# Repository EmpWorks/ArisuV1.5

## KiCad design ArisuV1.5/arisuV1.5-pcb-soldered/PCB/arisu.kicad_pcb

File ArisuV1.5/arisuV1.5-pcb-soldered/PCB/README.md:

# ArisuV1.5 Keyboard PCB
アリス PCB designed using KiCad. The layout is inspired by Lyn's EM7 and TGR Alice with some modification of my own.
Originally created by FateNozomi
### Disclaimer 
This board is a heavily-modified FateNozomi arisu-pcb While the schematic, basic layout etc is essentially the same, it supports additional features like Hot-swap,USB-C etc.

Key differences:
- supports hotswap PCB sockets
- added WS2812B Smd Led footprint for backlit 
- encoder support
- supports atmega32u4 MU/AU
- USB-C compatibility

Disclaimer: Use these files at your own risk.

## Assembly
For the components required, you may refer to the bill of materials here [BOM](https://github.com/donttellmywife1510/ArisuV1.5/blob/main/ArisuV1.5/arisuV1.5-pcb-soldered/PCB/arisu_BOM.xlsx).

All the components can be soldered using a regular soldering iron, lcsc parts list is for reference only.

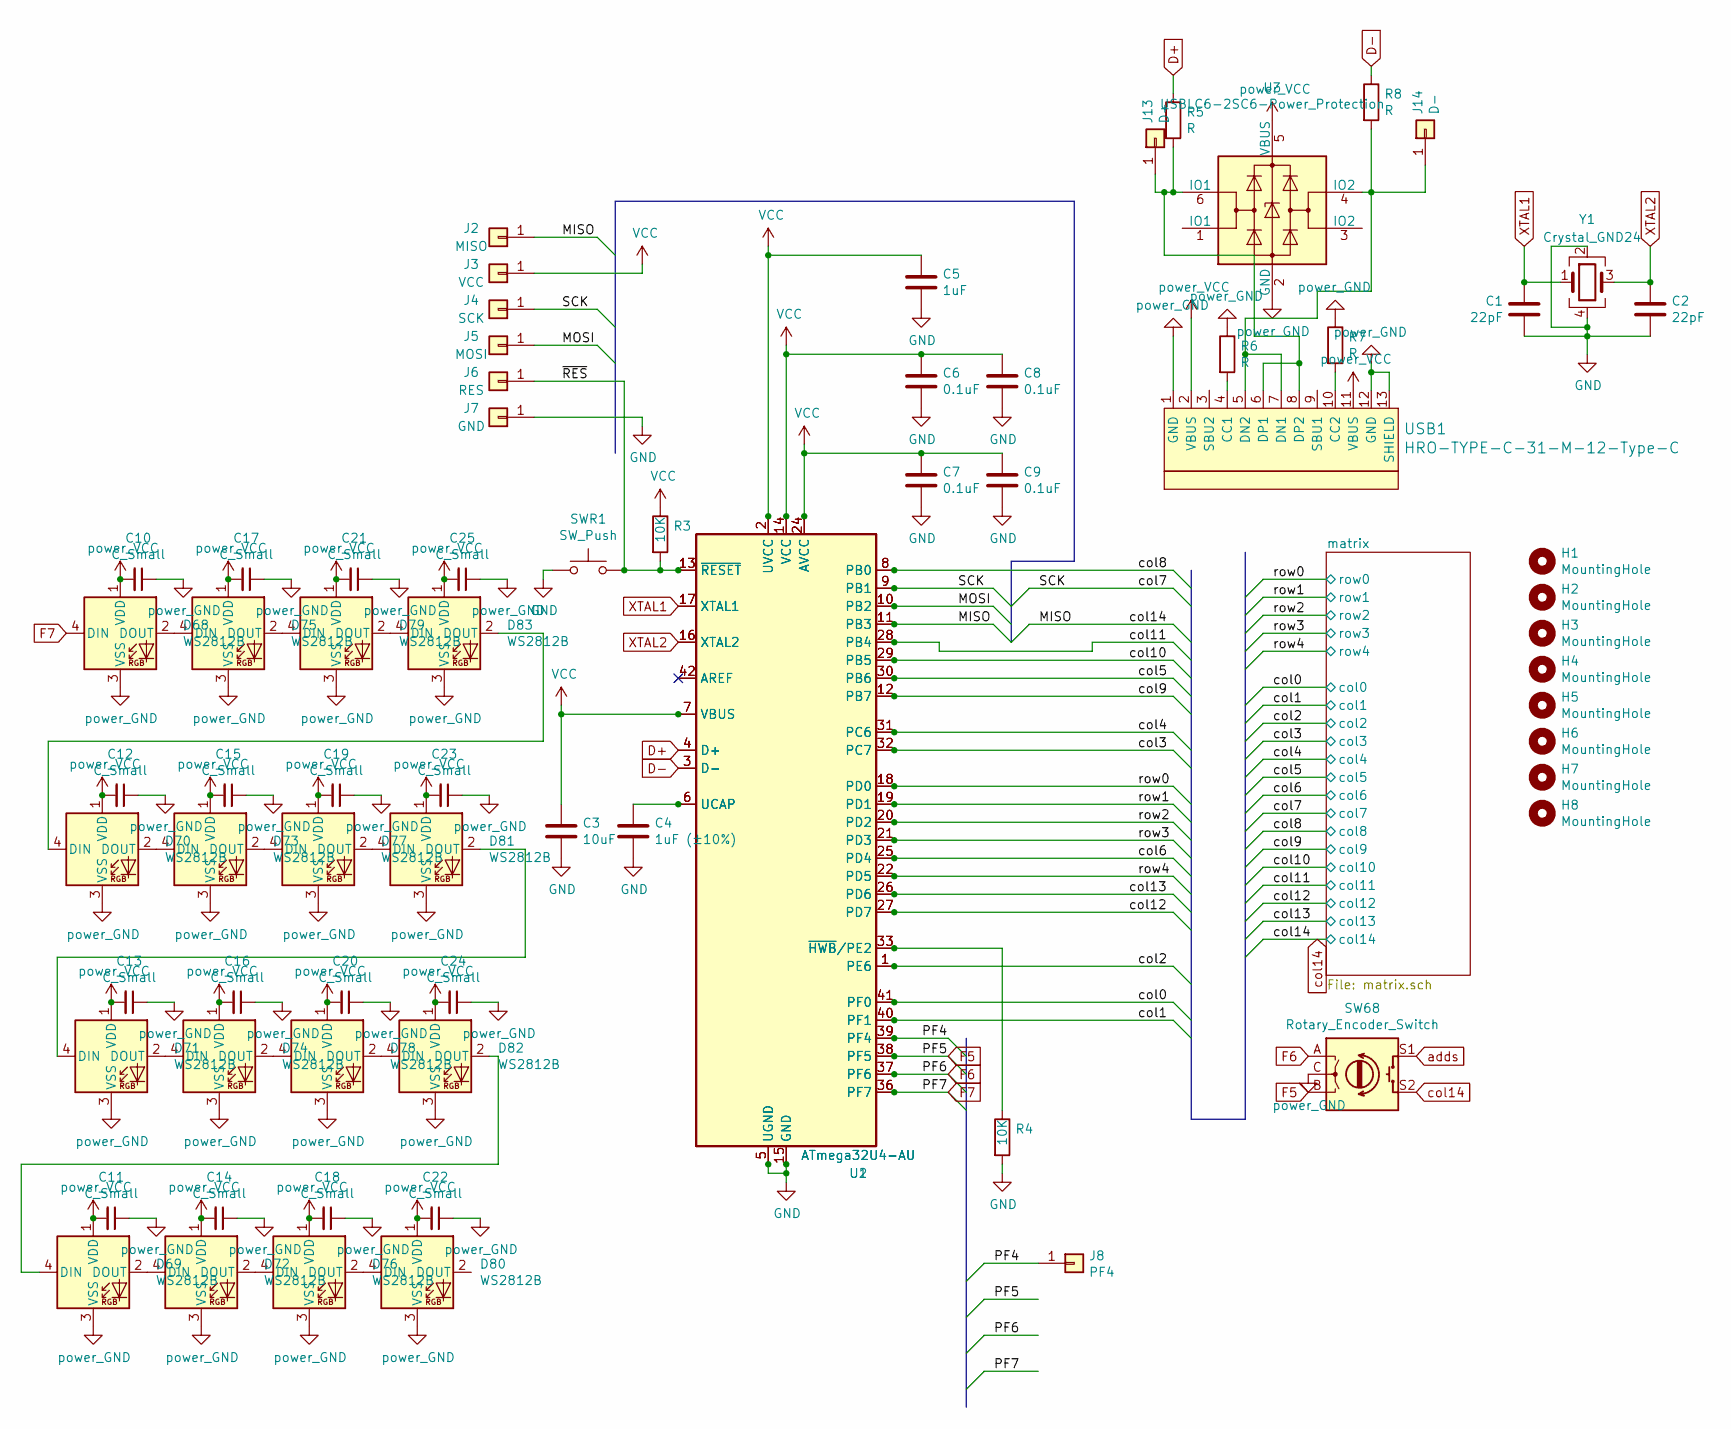
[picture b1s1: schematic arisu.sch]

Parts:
C1, C2: 22pF; C_0805_HandSoldering
C3: 10uF; C_0805_HandSoldering
C4: 1uF (±10%); C_0805_HandSoldering
C5: 1uF; C_0805_HandSoldering
C6, C7, C8, C9: 0.1uF; C_0805_HandSoldering
C10, C11, C12, C13, C14, C15, C16, C17, C18, C19, C20, C21, C22, C23, C24, C25: C_Small; C_0805_2012Metric_Pad1.18x1.45mm_HandSolder
D68, D69, D70, D71, D72, D73, D74, D75, D76, D77, D78, D79, D80, D81, D82, D83: WS2812B; LED_WS2812B_PLCC4_5.0x5.0mm_P3.2mm
H1, H2, H3, H4, H5, H6, H7, H8: MountingHole; MountingHole_2.2mm_M2_Pad
J2: MISO; Pin_Header_Straight_1x01_Pitch2.54mm
J3: VCC; Pin_Header_Straight_1x01_Pitch2.54mm
J4: SCK; Pin_Header_Straight_1x01_Pitch2.54mm
J5: MOSI; Pin_Header_Straight_1x01_Pitch2.54mm
J6: RES; Pin_Header_Straight_1x01_Pitch2.54mm
J7: GND; Pin_Header_Straight_1x01_Pitch2.54mm
J8: PF4; Pin_Header_Straight_1x01_Pitch2.54mm
J13: D+; Pin_Header_Straight_1x01_Pitch2.54mm
J14: D-; Pin_Header_Straight_1x01_Pitch2.54mm
R3, R4: 10K; R_0805_HandSoldering
R5, R6, R7, R8: R; R_0805_2012Metric_Pad1.20x1.40mm_HandSolder
SW68: Rotary_Encoder_Switch; RotaryEncoder_Alps_EC12E-Switch_Vertical_H20mm
SWR1: SW_Push; SW_SPST_TL3342
U1: ATmega32U4-AU; QFN-44-1EP_7x7mm_P0.5mm_EP5.2x5.2mm
U2: ATmega32U4-AU; LQFP-44_10x10mm_P0.8mm
U3: USBLC6-2SC6-Power_Protection; SOT-23-6
USB1: HRO-TYPE-C-31-M-12-Type-C; USB_C_Receptacle_HRO_TYPE-C-31-M-12-HandSoldering
Y1: Crystal_GND24; Crystal_SMD_SeikoEpson_FA238-4pin_3.2x2.5mm_HandSoldering

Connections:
/MOSI: J5.1, U1.10 (PB2), U2.10 (PB2)
/PF4: J8.1, U1.39 (PF4), U2.39 (PF4)
/SCK: J4.1, U1.9 (PB1), U2.9 (PB1); also elsewhere on the board
/col0: U1.41 (PF0), U2.41 (PF0); also elsewhere on the board
/col1: U1.40 (PF1), U2.40 (PF1); also elsewhere on the board
/col2: U1.1 (PE6), U2.1 (PE6); also elsewhere on the board
/col3: U1.32 (PC7), U2.32 (PC7); also elsewhere on the board
/col4: U1.31 (PC6), U2.31 (PC6); also elsewhere on the board
/col5: U1.30 (PB6), U2.30 (PB6); also elsewhere on the board
/col6: U1.25 (PD4), U2.25 (PD4); also elsewhere on the board
/col8: U1.8 (PB0), U2.8 (PB0); also elsewhere on the board
/col9: U1.12 (PB7), U2.12 (PB7); also elsewhere on the board
/col10: U1.29 (PB5), U2.29 (PB5); also elsewhere on the board
/col11: U1.28 (PB4), U2.28 (PB4); also elsewhere on the board
/col12: U1.27 (PD7), U2.27 (PD7); also elsewhere on the board
/col13: U1.26 (PD6), U2.26 (PD6); also elsewhere on the board
/row0: U1.18 (PD0), U2.18 (PD0); also elsewhere on the board
/row1: U1.19 (PD1), U2.19 (PD1); also elsewhere on the board
/row2: U1.20 (PD2), U2.20 (PD2); also elsewhere on the board
/row3: U1.21 (PD3), U2.21 (PD3); also elsewhere on the board
/row4: U1.22 (PD5), U2.22 (PD5); also elsewhere on the board
/~RES~: J6.1, R3.2, SWR1.2, U1.13 (~RESET), U2.13 (~RESET)
D+: R5.1, U1.4 (D+), U2.4 (D+)
D-: R8.1, U1.3 (D-), U2.3 (D-)
F5: SW68.B, U1.38 (PF5), U2.38 (PF5)
F6: SW68.A, U1.37 (PF6), U2.37 (PF6)
F7: D68.4 (DIN), U1.36 (PF7), U2.36 (PF7)
unnamed: C4.1, U1.6 (UCAP), U2.6 (UCAP)
unnamed: D68.2 (DOUT), D75.4 (DIN)
unnamed: D69.2 (DOUT), D72.4 (DIN)
unnamed: D69.4 (DIN), D82.2 (DOUT)
unnamed: D70.2 (DOUT), D73.4 (DIN)
unnamed: D70.4 (DIN), D83.2 (DOUT)
unnamed: D71.2 (DOUT), D74.4 (DIN)
unnamed: D71.4 (DIN), D81.2 (DOUT)
unnamed: D72.2 (DOUT), D76.4 (DIN)
unnamed: D73.2 (DOUT), D77.4 (DIN)
unnamed: D74.2 (DOUT), D78.4 (DIN)
unnamed: D75.2 (DOUT), D79.4 (DIN)
unnamed: D76.2 (DOUT), D80.4 (DIN)
unnamed: D77.2 (DOUT), D81.4 (DIN)
unnamed: D78.2 (DOUT), D82.4 (DIN)
unnamed: D79.2 (DOUT), D83.4 (DIN)
unnamed 109: J13.1, R5.2, U3.6 (IO1), USB1.6 (DP1), USB1.8 (DP2); also elsewhere on the board
unnamed 110: J14.1, R8.2, U3.4 (IO2), USB1.5 (DN2), USB1.7 (DN1); also elsewhere on the board
unnamed: R4.1, U1.33 (~HWB~/PE2), U2.33 (~HWB~/PE2)
unnamed: R6.2, USB1.4 (CC1)
unnamed: R7.2, USB1.10 (CC2)
unnamed: U1.42 (AREF), U2.42 (AREF)
XTAL1: C1.2, U1.17 (XTAL1), U2.17 (XTAL1), Y1.1
XTAL2: C2.1, U1.16 (XTAL2), U2.16 (XTAL2), Y1.3
adds: SW68.S1; also elsewhere on the board
col14: J2.1, SW68.S2, U1.11 (PB3), U2.11 (PB3); also elsewhere on the board

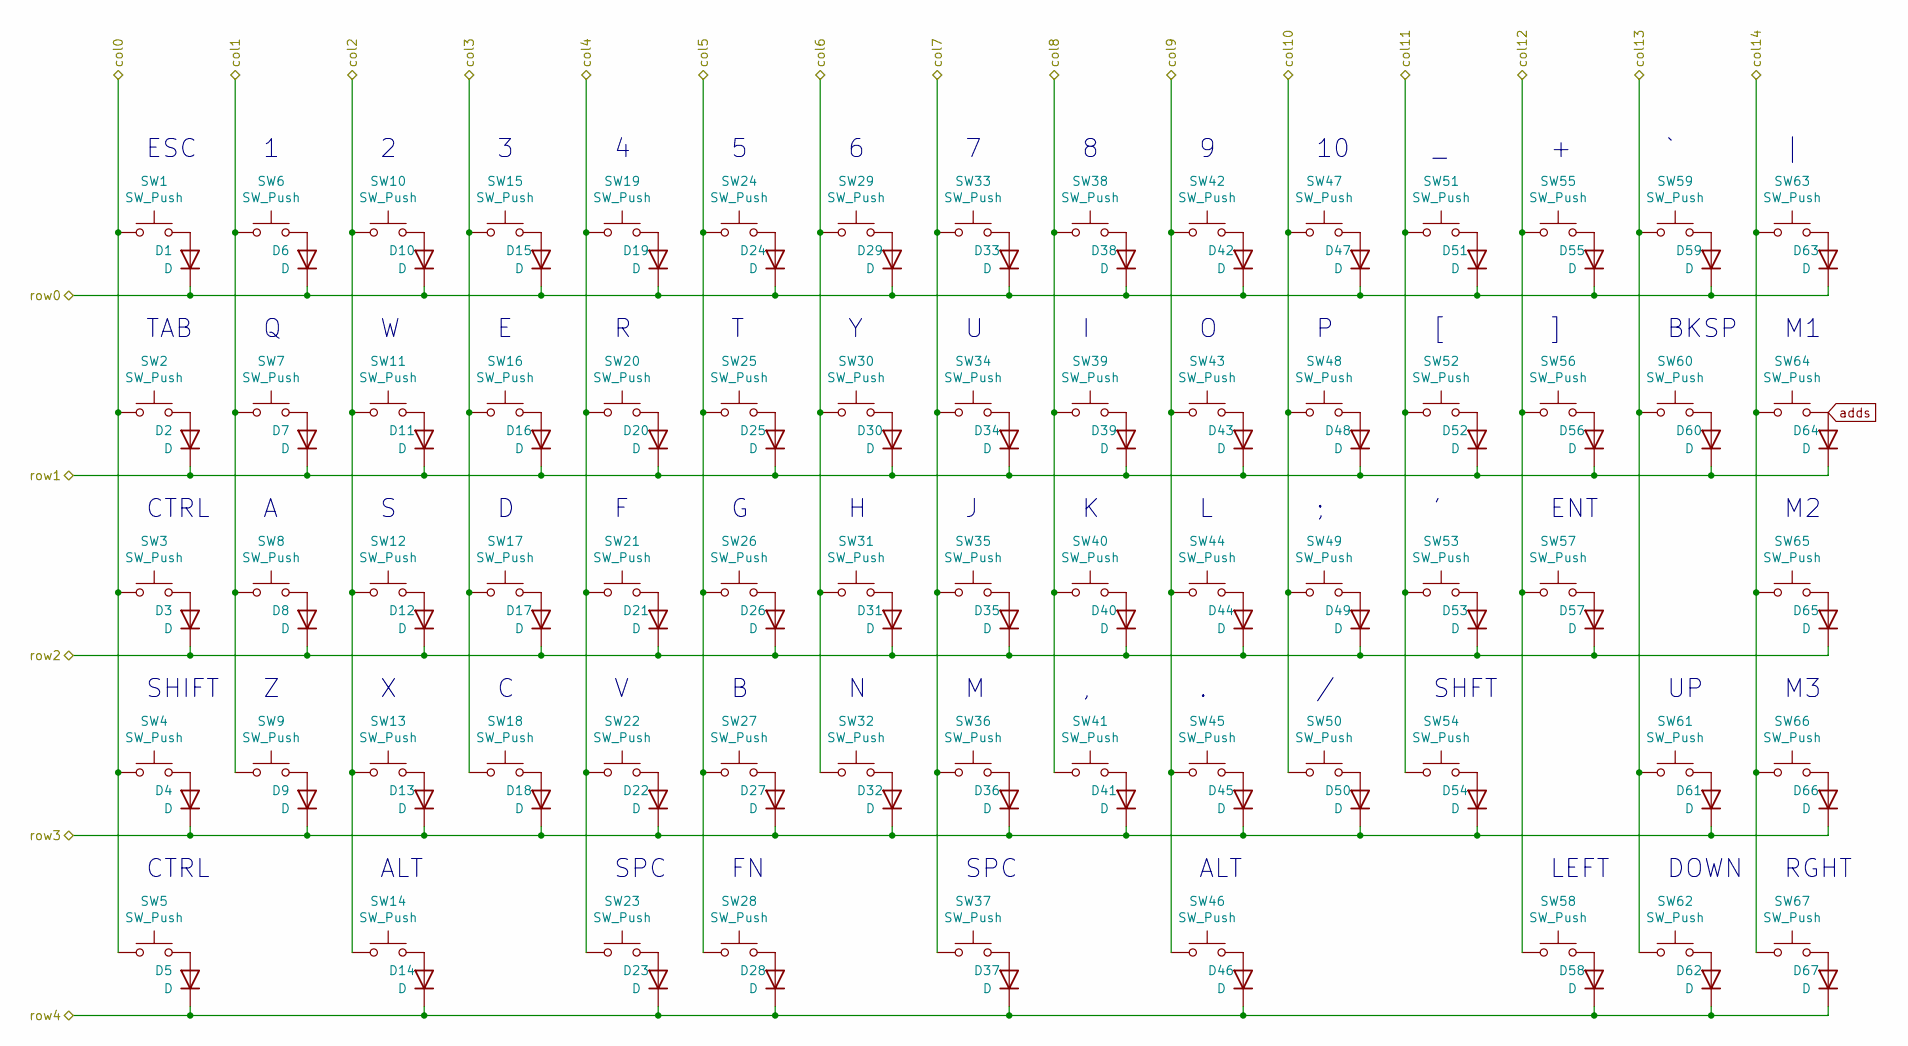
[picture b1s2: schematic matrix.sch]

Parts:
D1, D2, D3, D4, D5, D6, D7, D8, D9, D10, D11, D12, D13, D14, D15, D16, D17, D18, D19, D20, D21, D22, D23, D24, D25, D26, D27, D28, D29, D30, D31, D32, D33, D34, D35, D36, D37, D38, D39, D40, D41, D42, D43, D44, D45, D46, D47, D48, D49, D50, D51, D52, D53, D54, D55, D56, D57, D58, D59, D60, D61, D62, D63, D64, D65, D66, D67: D; D_SOD-123
SW1, SW6, SW7, SW8, SW9, SW10, SW11, SW12, SW13, SW15, SW16, SW17, SW18, SW19, SW20, SW21, SW22, SW24, SW25, SW26, SW27, SW28, SW29, SW30, SW31, SW32, SW33, SW34, SW35, SW36, SW38, SW39, SW40, SW41, SW42, SW43, SW44, SW45, SW47, SW48, SW49, SW50, SW51, SW52, SW53, SW55, SW56, SW58, SW59, SW61, SW62, SW63, SW64, SW65, SW66, SW67: SW_Push; SW_Cherry_MX_1.00u_PCB
SW2, SW5, SW14, SW46, SW60: SW_Push; SW_Cherry_MX_1.50u_PCB
SW3, SW54: SW_Push; SW_Cherry_MX_1.75u_PCB
SW4: SW_Push; SW_Cherry_MX_2.25u_PCB
SW23: SW_Push; SW_Cherry_MX_2.00u_PCB_ReversedStabilizers
SW37: SW_Push; SW_Cherry_MX_2.75u_PCB_ReversedStabilizers
SW57: SW_Push; SW_Cherry_MX_2.25u_PCB_ReversedStabilizers

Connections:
/SCK: SW33.1, SW34.1, SW35.1, SW36.1, SW37.1; also elsewhere on the board
/col0: SW1.1, SW2.1, SW3.1, SW4.1, SW5.1; also elsewhere on the board
/col1: SW6.1, SW7.1, SW8.1, SW9.1; also elsewhere on the board
/col2: SW10.1, SW11.1, SW12.1, SW13.1, SW14.1; also elsewhere on the board
/col3: SW15.1, SW16.1, SW17.1, SW18.1; also elsewhere on the board
/col4: SW19.1, SW20.1, SW21.1, SW22.1, SW23.1; also elsewhere on the board
/col5: SW24.1, SW25.1, SW26.1, SW27.1, SW28.1; also elsewhere on the board
/col6: SW29.1, SW30.1, SW31.1, SW32.1; also elsewhere on the board
/col8: SW38.1, SW39.1, SW40.1, SW41.1; also elsewhere on the board
/col9: SW42.1, SW43.1, SW44.1, SW45.1, SW46.1; also elsewhere on the board
/col10: SW47.1, SW48.1, SW49.1, SW50.1; also elsewhere on the board
/col11: SW51.1, SW52.1, SW53.1, SW54.1; also elsewhere on the board
/col12: SW55.1, SW56.1, SW57.1, SW58.1; also elsewhere on the board
/col13: SW59.1, SW60.1, SW61.1, SW62.1; also elsewhere on the board
/row0: D1.1 (K), D6.1 (K), D10.1 (K), D15.1 (K), D19.1 (K), D24.1 (K), D29.1 (K), D33.1 (K), D38.1 (K), D42.1 (K), D47.1 (K), D51.1 (K), D55.1 (K), D59.1 (K), D63.1 (K); also elsewhere on the board
/row1: D2.1 (K), D7.1 (K), D11.1 (K), D16.1 (K), D20.1 (K), D25.1 (K), D30.1 (K), D34.1 (K), D39.1 (K), D43.1 (K), D48.1 (K), D52.1 (K), D56.1 (K), D60.1 (K), D64.1 (K); also elsewhere on the board
/row2: D3.1 (K), D8.1 (K), D12.1 (K), D17.1 (K), D21.1 (K), D26.1 (K), D31.1 (K), D35.1 (K), D40.1 (K), D44.1 (K), D49.1 (K), D53.1 (K), D57.1 (K), D65.1 (K); also elsewhere on the board
/row3: D4.1 (K), D9.1 (K), D13.1 (K), D18.1 (K), D22.1 (K), D27.1 (K), D32.1 (K), D36.1 (K), D41.1 (K), D45.1 (K), D50.1 (K), D54.1 (K), D61.1 (K), D66.1 (K); also elsewhere on the board
/row4: D5.1 (K), D14.1 (K), D23.1 (K), D28.1 (K), D37.1 (K), D46.1 (K), D58.1 (K), D62.1 (K), D67.1 (K); also elsewhere on the board
unnamed: D1.2 (A), SW1.2
unnamed: D2.2 (A), SW2.2
unnamed: D3.2 (A), SW3.2
unnamed: D4.2 (A), SW4.2
unnamed: D5.2 (A), SW5.2
unnamed: D6.2 (A), SW6.2
unnamed: D7.2 (A), SW7.2
unnamed: D8.2 (A), SW8.2
unnamed: D9.2 (A), SW9.2
unnamed: D10.2 (A), SW10.2
unnamed: D11.2 (A), SW11.2
unnamed: D12.2 (A), SW12.2
unnamed: D13.2 (A), SW13.2
unnamed: D14.2 (A), SW14.2
unnamed: D15.2 (A), SW15.2
unnamed: D16.2 (A), SW16.2
unnamed: D17.2 (A), SW17.2
unnamed: D18.2 (A), SW18.2
unnamed: D19.2 (A), SW19.2
unnamed: D20.2 (A), SW20.2
unnamed: D21.2 (A), SW21.2
unnamed: D22.2 (A), SW22.2
unnamed: D23.2 (A), SW23.2
unnamed: D24.2 (A), SW24.2
unnamed: D25.2 (A), SW25.2
unnamed: D26.2 (A), SW26.2
unnamed: D27.2 (A), SW27.2
unnamed: D28.2 (A), SW28.2
unnamed: D29.2 (A), SW29.2
unnamed: D30.2 (A), SW30.2
unnamed: D31.2 (A), SW31.2
unnamed: D32.2 (A), SW32.2
unnamed: D33.2 (A), SW33.2
unnamed: D34.2 (A), SW34.2
unnamed: D35.2 (A), SW35.2
unnamed: D36.2 (A), SW36.2
unnamed: D37.2 (A), SW37.2
unnamed: D38.2 (A), SW38.2
unnamed: D39.2 (A), SW39.2
unnamed: D40.2 (A), SW40.2
unnamed: D41.2 (A), SW41.2
unnamed: D42.2 (A), SW42.2
unnamed: D43.2 (A), SW43.2
unnamed: D44.2 (A), SW44.2
unnamed: D45.2 (A), SW45.2
unnamed: D46.2 (A), SW46.2
unnamed: D47.2 (A), SW47.2
unnamed: D48.2 (A), SW48.2
unnamed: D49.2 (A), SW49.2
unnamed: D50.2 (A), SW50.2
unnamed: D51.2 (A), SW51.2
unnamed: D52.2 (A), SW52.2
unnamed: D53.2 (A), SW53.2
unnamed: D54.2 (A), SW54.2
unnamed: D55.2 (A), SW55.2
unnamed: D56.2 (A), SW56.2
unnamed: D57.2 (A), SW57.2
unnamed: D58.2 (A), SW58.2
unnamed: D59.2 (A), SW59.2
unnamed: D60.2 (A), SW60.2
unnamed: D61.2 (A), SW61.2
unnamed: D62.2 (A), SW62.2
unnamed: D63.2 (A), SW63.2
unnamed: D65.2 (A), SW65.2
unnamed: D66.2 (A), SW66.2
unnamed: D67.2 (A), SW67.2
adds: D64.2 (A), SW64.2; also elsewhere on the board
col14: SW63.1, SW64.1, SW65.1, SW66.1, SW67.1; also elsewhere on the board

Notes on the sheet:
ESC
TAB
BKSP
CTRL
ENT
SHIFT
SHFT
ALT
SPC
DOWN
LEFT
RGHT

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
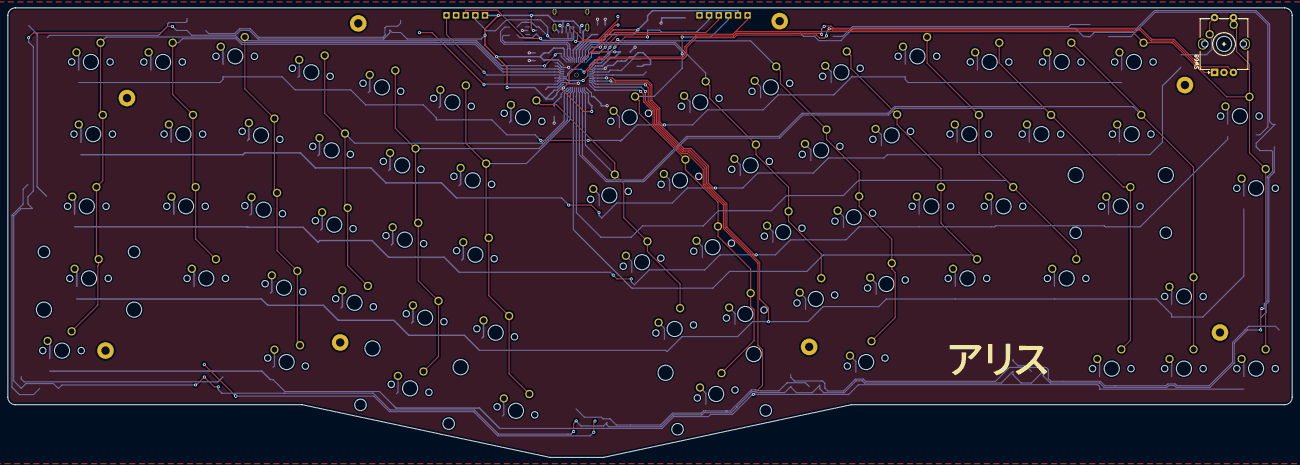
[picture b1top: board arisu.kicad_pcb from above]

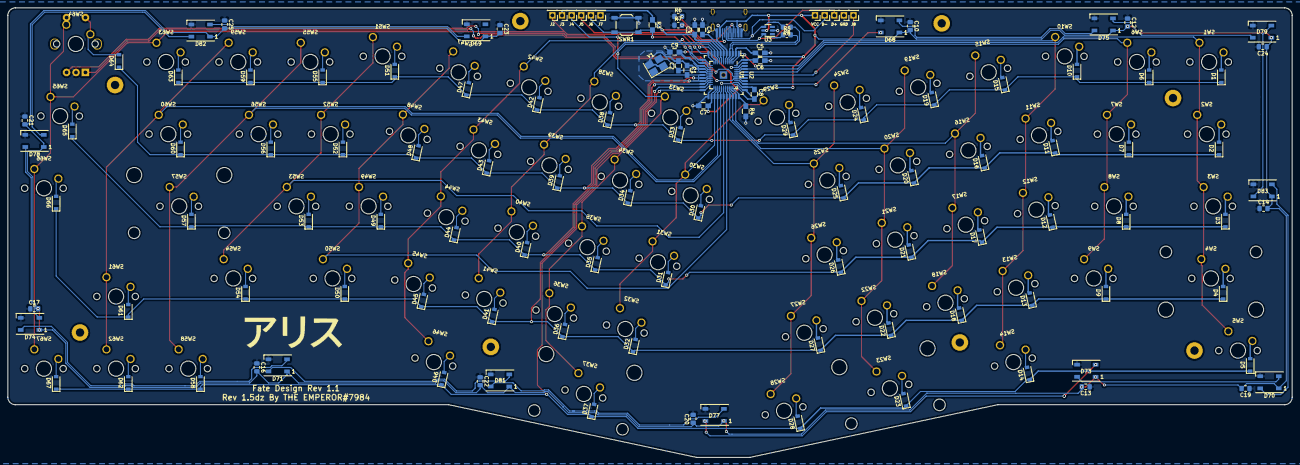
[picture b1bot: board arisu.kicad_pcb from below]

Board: 2 copper layers, 339.1 x 118.7 mm, 202 parts (125 on the bottom side), 118 nets.

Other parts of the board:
D+: D+; Pin_Header_Straight_1x01_Pitch2.54mm
D-: D-; Pin_Header_Straight_1x01_Pitch2.54mm
GND: GND; Pin_Header_Straight_1x01_Pitch2.54mm
H5#2: MountingHole; MountingHole_2.2mm_M2_Pad
VCC: VCC; Pin_Header_Straight_1x01_Pitch2.54mm

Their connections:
unnamed 109: D+.1; also elsewhere on the board
unnamed 110: D-.1; also elsewhere on the board
